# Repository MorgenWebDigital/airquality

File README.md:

# AirQuality

A battery-powered indoor air quality monitor. Real CO₂ from a photoacoustic
sensor, VOC and NOx, temperature, humidity and ambient light, shown on a 2.13"
e-paper display and sent over Bluetooth LE.

Two layers, 45 × 95 mm, 76 electrical components, one 21700 lithium cell.

| front | back |
|---|---|
|  |  |

---

## 1. What it measures

| Sensor | Measures | Accuracy | I²C |
|---|---|---|---|
| **SCD40** | CO₂, photoacoustic, a real measurement rather than an estimate | ±(50 ppm + 5 % of reading) | `0x62` |
| **SGP41** | VOC and NOx index | index, not a concentration | `0x59` |
| **SHT41** | humidity and temperature | ±1.8 %RH, ±0.2 °C | `0x44` |
| **T117Z** | temperature, the precision channel | ±0.1 °C, 16 bit | `0x48` |
| **BH1750** | ambient light | 1 lx resolution, 1–65535 lx | `0x23` |
| **MAX17048** | state of charge of the cell | ±1 %, no shunt needed | `0x36` |
| **BQ25895** | charger status and control | - | `0x6A` |

Everything shares one I²C bus. The addresses do not collide.

The SCD40 is the only sensor that measures CO₂ directly. The SGP41 reports a
VOC and a NOx index derived from a heated metal-oxide cell. That reads as "the
air is getting stale", and is not comparable to a ppm figure.

The full schematic as a PDF is in [`docs/schematic.pdf`](docs/schematic.pdf).

---

## 2. How the power works

```text
   USB-C ──▶ CH224K ──▶ VBUS ──▶ BQ25895 ──▶ SYS ──▶ XC6222 ──▶ 3.3 V
             requests            charger            LDO         MCU, sensors,
             9 V over PD                                        display
                                    │
                                    ▼
                                  21700 cell
                                    │
                              DW01A + FS8205A
                              cell protection
```

The **CH224K** negotiates 9 V over USB Power Delivery. At 9 V the charger draws
about half the current it would at 5 V for the same charging power. Less loss
in the cable, less heat. A 6.8 kΩ resistor on CFG1 selects the voltage; the
value comes straight from the table in the CH224K datasheet.

The **BQ25895** is a switching charger, not a linear one. It can deliver up to
5 A; the input current limit is set by a 250 Ω resistor to about 2.1 A. It also
provides the power path, so the device runs from USB while charging.

The cell is a **Molicel INR21700-P45B**, which ships unprotected. **DW01A** with
an **FS8205A** dual MOSFET adds over-charge, over-discharge and over-current
protection. A 1 kΩ resistor sits between the DW01A's VM pin and the pack
negative, as the datasheet's application circuit requires. Without it, plugging
in a charger while the protection has tripped puts the full charger voltage on
that pin with nothing to limit the current.

The **XC6222** drops SYS to 3.3 V. Its CE pin is tied to SYS: the regulator is
always on while the cell has charge. It cannot be switched off from the ESP32,
because the ESP32 hangs on that same rail and could never switch it back on.

---

## 3. The display

A 2.13" e-paper panel (GDEY0213B74, SSD1680 controller) on a 24-pin 0.5 mm FPC
connector. Bistable: it holds the image with no power at all, and only draws
current while updating.

The panel needs gate and source rails well beyond 3.3 V. They are generated on
the board, following the reference circuit in the panel's datasheet:

- a boost converter produces **VGH**: a 47 µH inductor and an SI1308 MOSFET,
  driven by the panel's own GDR output with a 2.2 Ω sense resistor on RESE
- a charge pump off the same switching node produces the negative **VGL**
- the other rails (VSH1, VSH2, VSL, VCOM) come from the panel's internal
  regulators and only need decoupling

All seven capacitors on these rails are rated **25 V**. That is not decoration:
VGH runs above 20 V, and a standard 1 µF 0603 from the shelf is often a 6.3 or
16 V part.

**BS1 is tied low**, which selects 4-wire SPI, matching the SDA/SCL/CS/DC/RES
wiring used here.

**Update budget.** The panel is rated for one million updates *or* five years,
whichever comes first. At one update per minute the update budget is gone in
under two years; at three minutes and longer, the five-year limit is reached
first. Redrawing no more often than every three minutes, and only when a value
actually changes, keeps the panel inside both limits.

---

## 4. Board details

| | |
|---|---|
| Size | 45 × 95 mm |
| Layers | 2, 35 µm copper |
| Ground | pour on the back, 3306 mm² |
| Minimum clearance | 0.2 mm |
| Minimum track | 0.2 mm |
| Vias | 0.6 mm pad, 0.3 mm drill |

**The ESP32 antenna** sits at the board edge with a keep-out on both copper
layers. Nothing is routed through it: no track, no via, no pour.

**ESD protection** on the USB data lines: a USBLC6-2SC6 sits 1.9 mm from the
connector pads, with the signal routed *through* the device rather than
branched off it, and a ground via right at its ground pad. Both matter more
than they look: an ESD pulse rises in under a nanosecond, and every millimetre
of track between the connector and the clamp adds roughly 35 V of overshoot
that the ESP32 then sees.

**U12 (SGP41) is marked do-not-populate.** The footprint and routing are there;
the part is left off in the current build. Fitting it later needs no board
change.

---

## 5. Building one

Everything needed is in this repository.

**Boards.** [`production/AirQuality-gerber.zip`](production/) goes straight to a
fab house. Two layers, 1.6 mm, 35 µm copper, any standard process. The zip holds
the Gerbers and the Excellon drill files.

**Parts.** [`production/AirQuality-bom.csv`](production/) lists every component
with its LCSC number where one exists.
[`production/AirQuality-positions.csv`](production/) is the pick-and-place file.

**Datasheets** for every active part are in [`datasheets/`](datasheets/), named
by LCSC part number.

**Opening the design.** KiCad 9. Open
[`hardware/AirQuality.kicad_pro`](hardware/). All symbols, footprints and 3D
models live in `hardware/libraries/` and are referenced relatively, so the
project opens from any location.

**Mechanical.** [`docs/AirQuality.step`](docs/) is the full board with all
components, for enclosure design.

---

## 6. Design notes

Longer notes on why things are the way they are:

- [`docs/design-notes.md`](docs/design-notes.md): component choices and the
  reasoning behind them
- [`docs/track-widths.md`](docs/track-widths.md): current, trace widths and
  the IPC-2221 arithmetic

---

## 7. Verification

The board passes with no electrical findings:

```text
   ERC                      0 errors, 0 warnings
   Unconnected pads         0
   Shorts                   0
   Clearance violations     0
   Schematic parity         0
```

Every integrated circuit has been checked pin by pin against its datasheet. Not
against memory or a symbol's label, but against the document in
[`datasheets/`](datasheets/).

Remaining DRC output is silkscreen only: reference designators over copper and
part outlines crossing the board edge at the connectors. Neither affects
manufacture.

---

## 8. License

[PolyForm Noncommercial 1.0.0](LICENSE). Any use is permitted except a
commercial one.

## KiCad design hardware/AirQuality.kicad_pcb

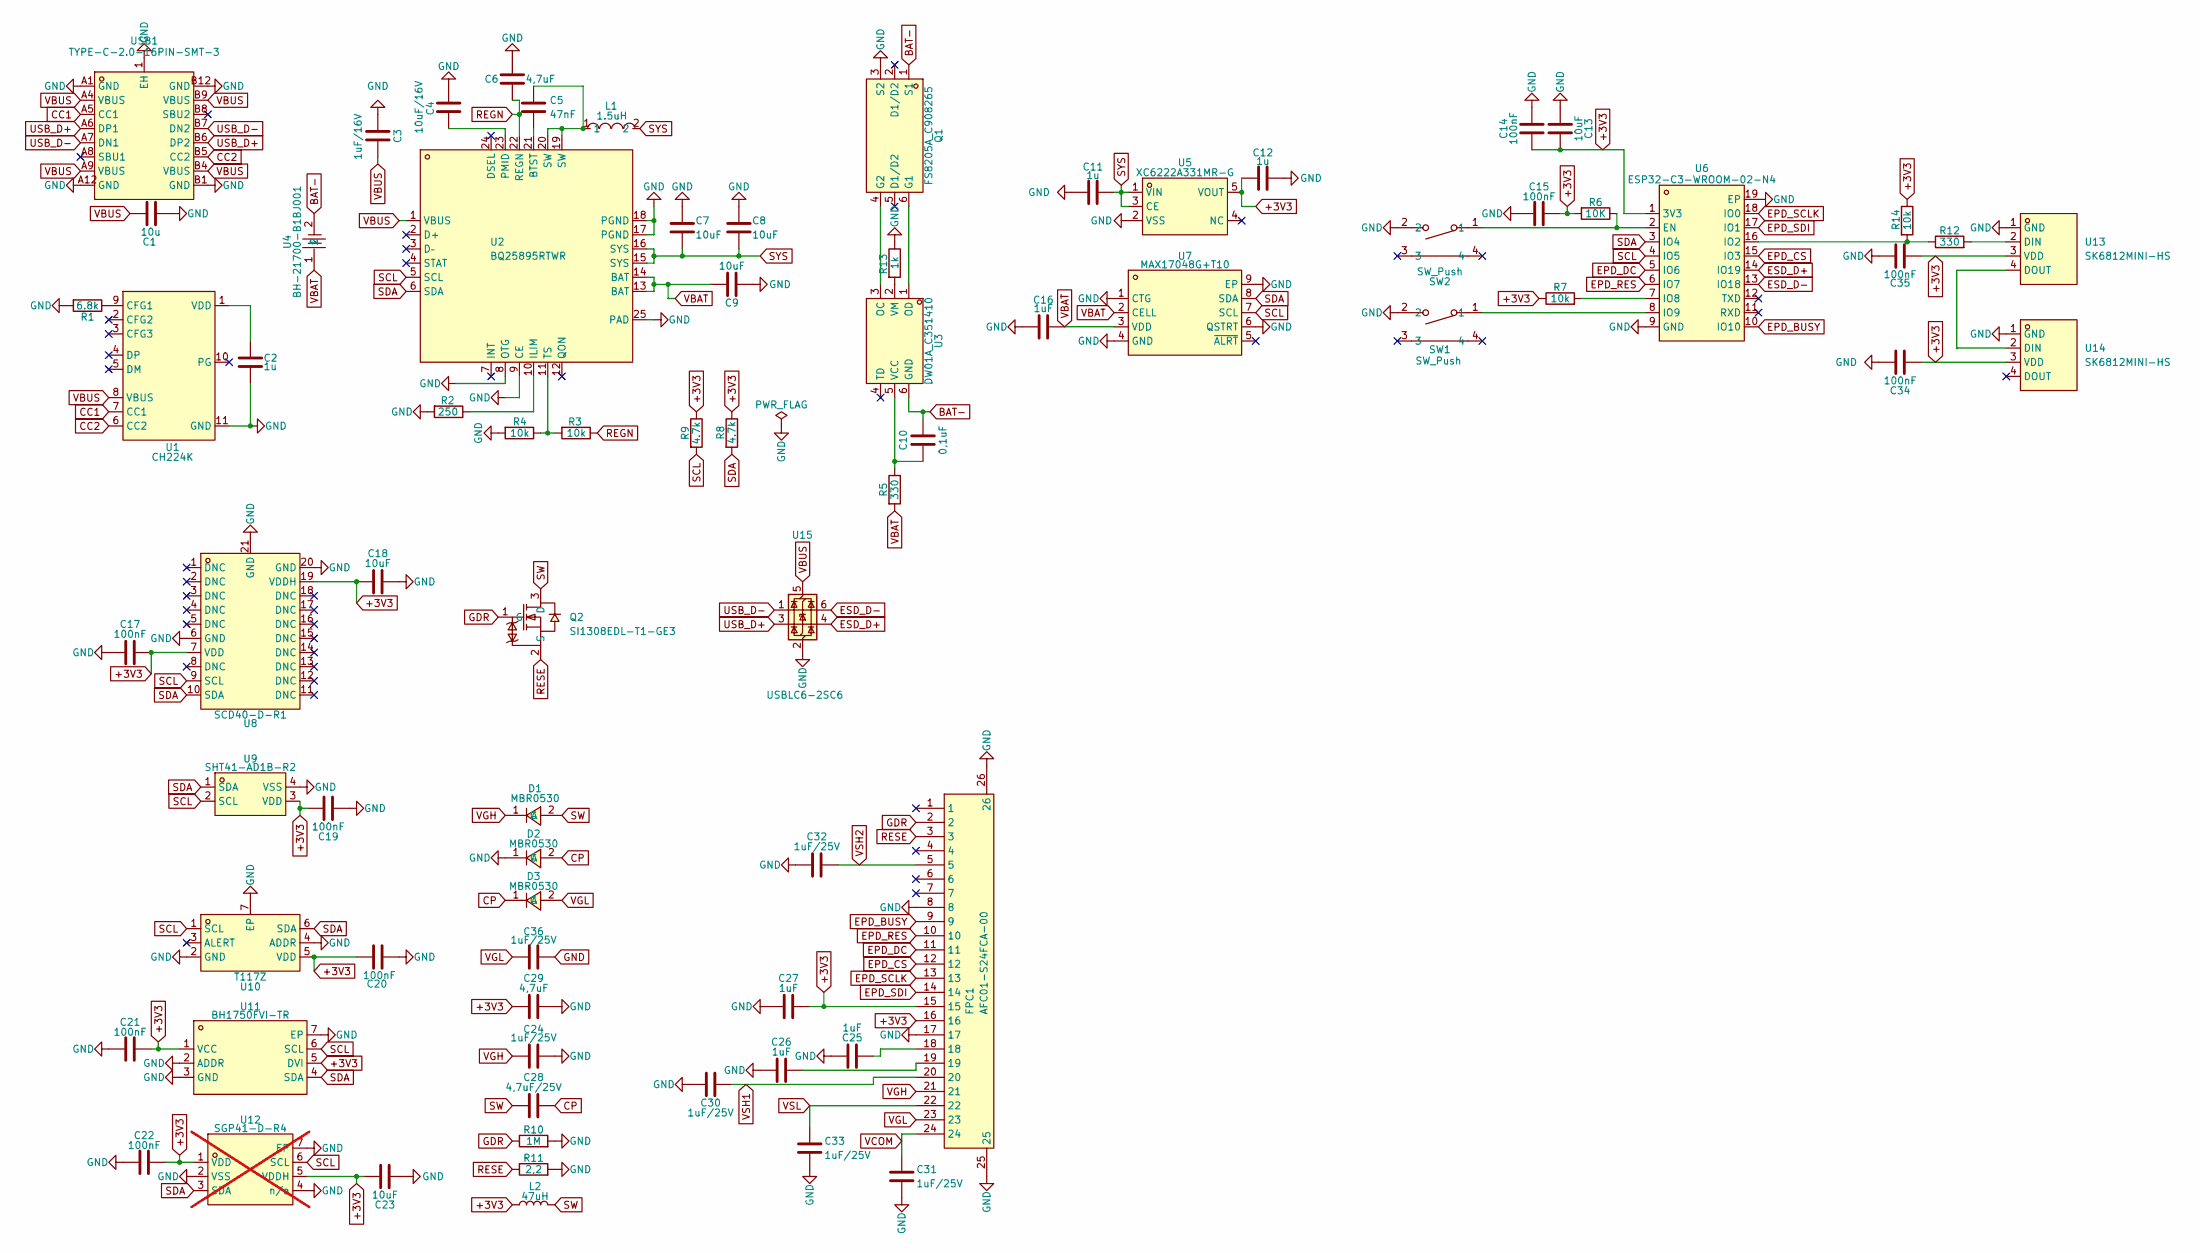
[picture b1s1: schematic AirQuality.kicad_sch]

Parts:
C1: 10u; C_0603_1608Metric
C2, C11, C12: 1u; C_0603_1608Metric
C3: 1uF/16V; C_0603_1608Metric
C4: 10uF/16V; C_0603_1608Metric
C5: 47nF; C_0603_1608Metric
C6, C29: 4,7uF; C_0603_1608Metric
C7, C8, C9, C13, C18, C23: 10uF; C_0603_1608Metric
C10: 0,1uF; C_0603_1608Metric
C14, C15, C17, C19, C20, C21, C22, C34, C35: 100nF; C_0603_1608Metric
C16, C25, C26, C27: 1uF; C_0603_1608Metric
C24, C30, C31, C32, C33, C36: 1uF/25V; C_0603_1608Metric
C28: 4,7uF/25V; C_0603_1608Metric
D1, D2, D3: MBR0530; SOD-123_L2.8-W1.8-LS3.7-RD; MPN MBR0530; LCSC Part C77336
FPC1: AFC01-S24FCA-00; FPC-SMD_24P-P0.50_AFC01-S24FCA-00; MPN AFC01-S24FCA-00; LCSC Part C262669
L1: 1.5uH; IND-SMD_L5.0-W5.0_SWPA5040S; MPN SWPA5040S1R5NT; LCSC Part C96922
L2: 47uH; IND-SMD_L5.8-W5.2
Q1: FS8205A_C908265; SOT-23-6_L2.9-W1.6-P0.95-LS2.8-BR; MPN FS8205A; LCSC Part C908265
Q2: SI1308EDL-T1-GE3; SOT-323_L2.0-W1.3-P1.30-LS2.1-BR; MPN SI1308EDL-T1-GE3; LCSC Part C469327
R1: 6.8k; R_0603_1608Metric
R2: 250; R_0603_1608Metric
R3, R4, R7, R14: 10k; R_0603_1608Metric
R5, R12: 330; R_0603_1608Metric
R6: 10K; R_0603_1608Metric
R8, R9: 4.7k; R_0603_1608Metric
R10: 1M; R_0603_1608Metric
R11: 2,2; R_0603_1608Metric
R13: 1k; R_0402_1005Metric
SW1, SW2: SW_Push; SW-SMD_2P-TS24CA; MPN TS24CA; LCSC Part C393942
U1: CH224K; ESSOP-10_L4.9-W3.9-P1.0-LS6.0-TL-EP; MPN CH224K; LCSC Part C970725
U2: BQ25895RTWR; QFN-24_L4.0-W4.0-P0.50-TL-EP2.7; MPN BQ25895RTWR; LCSC Part C80200
U3: DW01A_C351410; SOT-23-6_L2.9-W1.6-P0.95-LS2.8-BL; MPN DW01A; LCSC Part C351410
U4: BH-21700-B1BJ001; BAT-SMD_L82.5.5-W25-BH-21700-B1BJ001; MPN BH-21700-B1BJ001; LCSC Part C20606791
U5: XC6222A331MR-G; SOT-25-5_L2.9-W1.6-P0.95-LS2.8-BR; MPN XC6222A331MR-G; LCSC Part C5375082
U6: ESP32-C3-WROOM-02-N4; BULETM-SMD_ESPRESSIF_ESP32-C3-WROOM-02-N4-4MB; MPN ESP32-C3-WROOM-02-N4; LCSC Part C2934560
U7: MAX17048G+T10; TDFN-8_L2.0-W2.0-P0.50-BL-EP1.2; MPN MAX17048G+T10; LCSC Part C2682616
U8: SCD40-D-R1; LGA-20_L10.1-W10.1-P1.25-TL; MPN SCD40-D-R1; LCSC Part C3037696
U9: SHT41-AD1B-R2; DFN-4_L1.5-W1.5-SHT41-AD1B-R2; MPN SHT41-AD1B-R2; LCSC Part C7461861
U10: T117Z; TDFN-6_L2.0-W2.0-P0.65-TL-EP; MPN T117Z; LCSC Part C19284876
U11: BH1750FVI-TR; WSOF-6_L2.6-W1.6-P0.50-TL-EP; MPN BH1750FVI-TR; LCSC Part C78960
U12: SGP41-D-R4; DFN-6_L2.4-W2.4-P0.80-TL-EP; MPN SGP41-D-R4; LCSC Part C3659325; not fitted
U13, U14: SK6812MINI-HS; LED-SMD_4P-L3.5-W3.5-BR_SK6812MINI-HS; MPN SK6812MINI-HS; LCSC Part C2922787
U15: USBLC6-2SC6; SOT-23-6
USB1: TYPE-C-2.0-16PIN-SMT-3; TYPE-C-SMD_TYPE-CF3.1; MPN TYPE-C-2.0-16PIN-SMT-3; LCSC Part C2987386

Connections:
+3V3: C12.1, C13.2, C14.2, C15.2, C17.2, C18.1, C19.1, C20.2, C21.2, C22.2, C23.1, C27.2, C29.1, C34.1, C35.1, FPC1.15, FPC1.16, L2.1, R6.2, R7.1, R8.1, R9.1, R14.1, U5.5 (VOUT), U6.1 (3V3), U8.7 (VDD), U8.19 (VDDH), U9.3 (VDD), U10.5 (VDD), U11.1 (VCC), U11.5 (DVI), U12.1 (VDD), U12.5 (VDDH), U13.3 (VDD), U14.3 (VDD)
BAT-: C10.1, Q1.1 (S1), U3.6 (GND), U4.2
CC1: U1.7 (CC1), USB1.A5 (CC1)
CC2: U1.6 (CC2), USB1.B5 (CC2)
CP: C28.2, D2.2 (A), D3.1 (C)
EPD_BUSY: FPC1.9, U6.10 (IO10)
EPD_CS: FPC1.12, U6.15 (IO3)
EPD_DC: FPC1.11, U6.5 (IO6)
EPD_RES: FPC1.10, U6.6 (IO7)
EPD_SCLK: FPC1.13, U6.18 (IO0)
EPD_SDI: FPC1.14, U6.17 (IO1)
ESD_D+: U6.14 (IO19), U15.4 (I/O2)
ESD_D-: U6.13 (IO18), U15.6 (I/O1)
GDR: FPC1.2, Q2.1 (G), R10.1
GND: C1.2, C2.2, C3.2, C4.2, C6.1, C7.1, C8.1, C9.1, C11.1, C12.2, C13.1, C14.1, C15.1, C16.1, C17.1, C18.2, C19.2, C20.1, C21.1, C22.1, C23.2, C24.2, C25.2, C26.1, C27.1, C29.2, C30.1, C31.2, C32.1, C33.2, C34.2, C35.2, C36.2, D2.1 (C), FPC1.8, FPC1.17, FPC1.25, FPC1.26, Q1.3 (S2), R1.2, R2.2, R4.2, R10.2, R11.2, R13.1, SW1.2, SW2.2, U1.11 (GND), U2.8 (OTG), U2.9 (CE), U2.17 (PGND), U2.18 (PGND), U2.25 (PAD), U5.2 (VSS), U6.9 (GND), U6.19 (EP), U7.1 (CTG), U7.4 (GND), U7.6 (QSTRT), U7.9 (EP), U8.6 (GND), U8.20 (GND), U8.21 (GND), U9.4 (VSS), U10.2 (GND), U10.4 (ADDR), U10.7 (EP), U11.2 (ADDR), U11.3 (GND), U11.7 (EP), U12.2 (VSS), U12.4 (n/a), U12.7 (EP), U13.1 (GND), U14.1 (GND), U15.2 (GND), USB1.1 (EH), USB1.A1 (GND), USB1.A12 (GND), USB1.B1 (GND), USB1.B12 (GND)
unnamed: C5.1, L1.1, U2.19 (SW), U2.20 (SW)
unnamed: C25.1, FPC1.18
unnamed: C26.2, FPC1.19
unnamed: Q1.6 (G1), U3.1 (OD)
unnamed: Q1.4 (G2), U3.3 (OC)
unnamed: R1.1, U1.9 (CFG1)
unnamed: C2.1, U1.1 (VDD)
unnamed: C5.2, U2.21 (BTST)
unnamed: R2.1, U2.10 (ILIM)
unnamed: C4.1, U2.23 (PMID)
unnamed: R3.2, R4.1, U2.11 (TS)
unnamed: C10.2, R5.1, U3.5 (VCC)
unnamed: R13.2, U3.2 (VM)
unnamed: R6.1, SW2.1, U6.2 (EN)
unnamed: R12.1, R14.2, U6.16 (IO2)
unnamed: R7.2, U6.7 (IO8)
unnamed: SW1.1, U6.8 (IO9)
unnamed: R12.2, U13.2 (DIN)
unnamed: U13.4 (DOUT), U14.2 (DIN)
REGN: C6.2, R3.1, U2.22 (REGN)
RESE: FPC1.3, Q2.2 (S), R11.1
SCL: R9.2, U2.5 (SCL), U6.4 (IO5), U7.7 (SCL), U8.9 (SCL), U9.2 (SCL), U10.1 (SCL), U11.6 (SCL), U12.6 (SCL)
SDA: R8.2, U2.6 (SDA), U6.3 (IO4), U7.8 (SDA), U8.10 (SDA), U9.1 (SDA), U10.6 (SDA), U11.4 (SDA), U12.3 (SDA)
SW: C28.1, D1.2 (A), L2.2, Q2.3 (D)
SYS: C7.2, C8.2, C11.2, L1.2, U2.15 (SYS), U2.16 (SYS), U5.1 (VIN), U5.3 (CE)
USB_D+: U15.3 (I/O2), USB1.A6 (DP1), USB1.B6 (DP2)
USB_D-: U15.1 (I/O1), USB1.A7 (DN1), USB1.B7 (DN2)
VBAT: C9.2, C16.2, R5.2, U2.13 (BAT), U2.14 (BAT), U4.1, U7.2 (CELL), U7.3 (VDD)
VBUS: C1.1, C3.1, U1.8 (VBUS), U2.1 (VBUS), U15.5 (VBUS), USB1.A4 (VBUS), USB1.A9 (VBUS), USB1.B4 (VBUS), USB1.B9 (VBUS)
VCOM: C31.1, FPC1.24
VGH: C24.1, D1.1 (C), FPC1.21
VGL: C36.1, D3.2 (A), FPC1.23
VSH1: C30.2, FPC1.20
VSH2: C32.2, FPC1.5
VSL: C33.1, FPC1.22

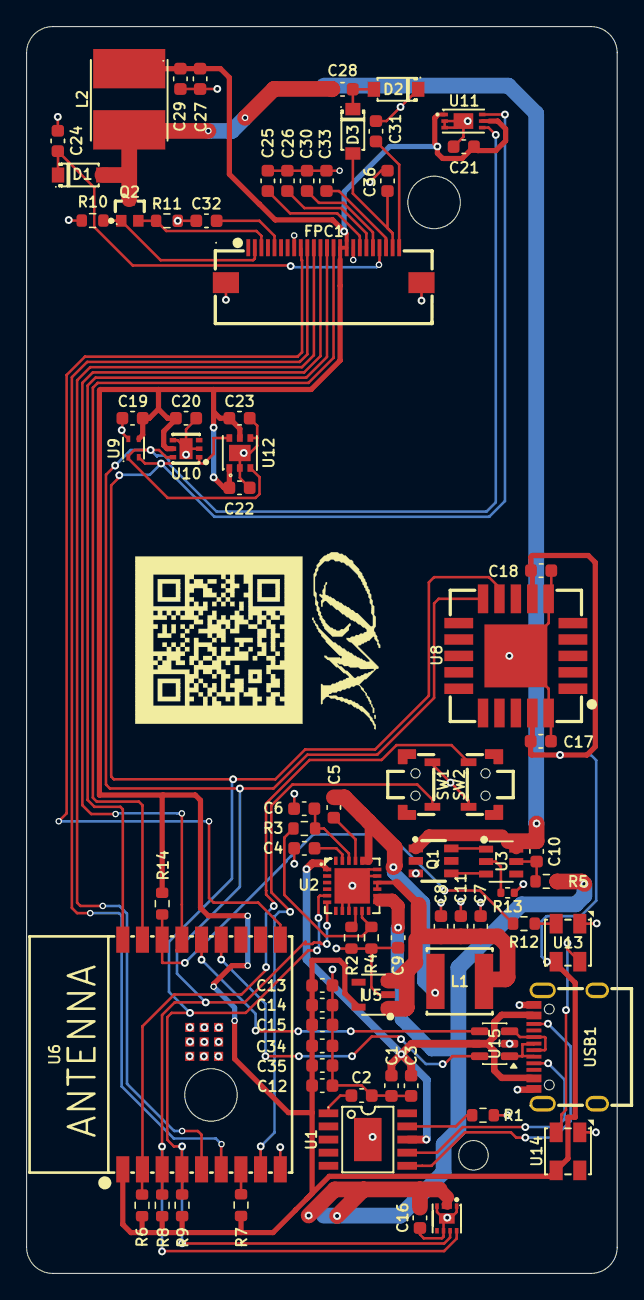
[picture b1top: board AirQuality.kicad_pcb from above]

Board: 2 copper layers, 45.0 x 95.0 mm, 78 parts (1 on the bottom side), 50 nets.

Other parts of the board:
LOGO: MWD_Logo
QR: https://github.com/MorgenWebDigital; MWD_QR_GitHub

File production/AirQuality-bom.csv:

"Reference","Value","Footprint","Quantity","LCSC","Datasheet"
"C1","10u","Capacitor_SMD:C_0603_1608Metric","1","","~"
"C2,C11,C12","1u","Capacitor_SMD:C_0603_1608Metric","3","","~"
"C3","1uF/16V","Capacitor_SMD:C_0603_1608Metric","1","","~"
"C4","10uF/16V","Capacitor_SMD:C_0603_1608Metric","1","","~"
"C5","47nF","Capacitor_SMD:C_0603_1608Metric","1","","~"
"C6,C29","4,7uF","Capacitor_SMD:C_0603_1608Metric","2","","~"
"C7-C9,C13,C18,C23","10uF","Capacitor_SMD:C_0603_1608Metric","6","","~"
"C10","0,1uF","Capacitor_SMD:C_0603_1608Metric","1","","~"
"C14,C15,C17,C19-C22,C34,C35","100nF","Capacitor_SMD:C_0603_1608Metric","9","","~"
"C16,C25-C27","1uF","Capacitor_SMD:C_0603_1608Metric","4","","~"
"C24,C30-C33,C36","1uF/25V","Capacitor_SMD:C_0603_1608Metric","6","","~"
"C28","4,7uF/25V","Capacitor_SMD:C_0603_1608Metric","1","","~"
"D1-D3","MBR0530","AirQuality:SOD-123_L2.8-W1.8-LS3.7-RD","3","C77336","https://lcsc.com/product-detail/Schottky-Barrier-Diodes-SBD_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"
"FPC1","AFC01-S24FCA-00","AirQuality:FPC-SMD_24P-P0.50_AFC01-S24FCA-00","1","C262669","https://lcsc.com/product-detail/FPC-Connectors_JUSHUO-AFC01-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"
"L1","1.5uH","AirQuality:IND-SMD_L5.0-W5.0_SWPA5040S","1","C96922","https://lcsc.com/product-detail/Power-Inductors_1-5uH-30_C96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"
"L2","47uH","AirQuality:IND-SMD_L5.8-W5.2","1","","~"
"Q1","FS8205A_C908265","AirQuality:SOT-23-6_L2.9-W1.6-P0.95-LS2.8-BR","1","C908265","https://lcsc.com/product-detail/MOSFET_FUXINSEMI-FS8205A_C90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"
"Q2","SI1308EDL-T1-GE3","AirQuality:SOT-323_L2.0-W1.3-P1.30-LS2.1-BR","1","C469327","https://www.lcsc.com/datasheet/C469327.pdf"
"R1","6.8k","Resistor_SMD:R_0603_1608Metric","1","","~"
"R2","250","Resistor_SMD:R_0603_1608Metric","1","","~"
"R3,R4,R7,R14","10k","Resistor_SMD:R_0603_1608Metric","4","","~"
"R5,R12","330","Resistor_SMD:R_0603_1608Metric","2","","~"
"R6","10K","Resistor_SMD:R_0603_1608Metric","1","","~"
"R8,R9","4.7k","Resistor_SMD:R_0603_1608Metric","2","","~"
"R10","1M","Resistor_SMD:R_0603_1608Metric","1","","~"
"R11","2,2","Resistor_SMD:R_0603_1608Metric","1","","~"
"R13","1k","Resistor_SMD:R_0402_1005Metric","1","","~"
"SW1,SW2","SW_Push","AirQuality:SW-SMD_2P-TS24CA","2","C393942","https://lcsc.com/product-detail/Tactile-Switches_SHOU-HAN-TS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"
"U1","CH224K","AirQuality:ESSOP-10_L4.9-W3.9-P1.0-LS6.0-TL-EP","1","C970725","https://www.lcsc.com/datasheet/C970725.pdf"
"U2","BQ25895RTWR","AirQuality:QFN-24_L4.0-W4.0-P0.50-TL-EP2.7","1","C80200","https://lcsc.com/product-detail/PMIC-Battery-Management_TI_B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"
"U3","DW01A_C351410","AirQuality:SOT-23-6_L2.9-W1.6-P0.95-LS2.8-BL","1","C351410","https://lcsc.com/product-detail/Others_PUOLOP-DW01_C351410.html"
"U4","BH-21700-B1BJ001","AirQuality:BAT-SMD_L82.5.5-W25-BH-21700-B1BJ001","1","C20606791","https://www.lcsc.com/datasheet/C20606791.pdf"
"U5","XC6222A331MR-G","AirQuality:SOT-25-5_L2.9-W1.6-P0.95-LS2.8-BR","1","C5375082","https://www.lcsc.com/datasheet/C5375082.pdf"
"U6","ESP32-C3-WROOM-02-N4","AirQuality:BULETM-SMD_ESPRESSIF_ESP32-C3-WROOM-02-N4-4MB","1","C2934560","https://www.lcsc.com/datasheet/C2934560.pdf"
"U7","MAX17048G+T10","AirQuality:TDFN-8_L2.0-W2.0-P0.50-BL-EP1.2","1","C2682616","https://www.lcsc.com/datasheet/C2682616.pdf"
"U8","SCD40-D-R1","AirQuality:LGA-20_L10.1-W10.1-P1.25-TL","1","C3037696","https://www.lcsc.com/datasheet/C3037696.pdf"
"U9","SHT41-AD1B-R2","AirQuality:DFN-4_L1.5-W1.5-SHT41-AD1B-R2","1","C7461861","https://www.lcsc.com/datasheet/C7461861.pdf"
"U10","T117Z","AirQuality:TDFN-6_L2.0-W2.0-P0.65-TL-EP","1","C19284876","https://www.lcsc.com/datasheet/C19284876.pdf"
"U11","BH1750FVI-TR","AirQuality:WSOF-6_L2.6-W1.6-P0.50-TL-EP","1","C78960","https://lcsc.com/product-detail/Sensors_ROHM_BH1750FVI-TR_BH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"
"U12","SGP41-D-R4","AirQuality:DFN-6_L2.4-W2.4-P0.80-TL-EP","1","C3659325","https://www.lcsc.com/datasheet/C3659325.pdf"
"U13,U14","SK6812MINI-HS","AirQuality:LED-SMD_4P-L3.5-W3.5-BR_SK6812MINI-HS","2","C2922787","https://www.lcsc.com/datasheet/C2922787.pdf"
"U15","USBLC6-2SC6","Package_TO_SOT_SMD:SOT-23-6","1","","https://www.st.com/resource/en/datasheet/usblc6-2.pdf"
"USB1","TYPE-C-2.0-16PIN-SMT-3","AirQuality:TYPE-C-SMD_TYPE-CF3.1","1","C2987386","https://www.lcsc.com/datasheet/C2987386.pdf"
